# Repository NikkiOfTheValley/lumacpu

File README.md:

# lumacpu
LumaCPU is a custom SBC created for fun/learning

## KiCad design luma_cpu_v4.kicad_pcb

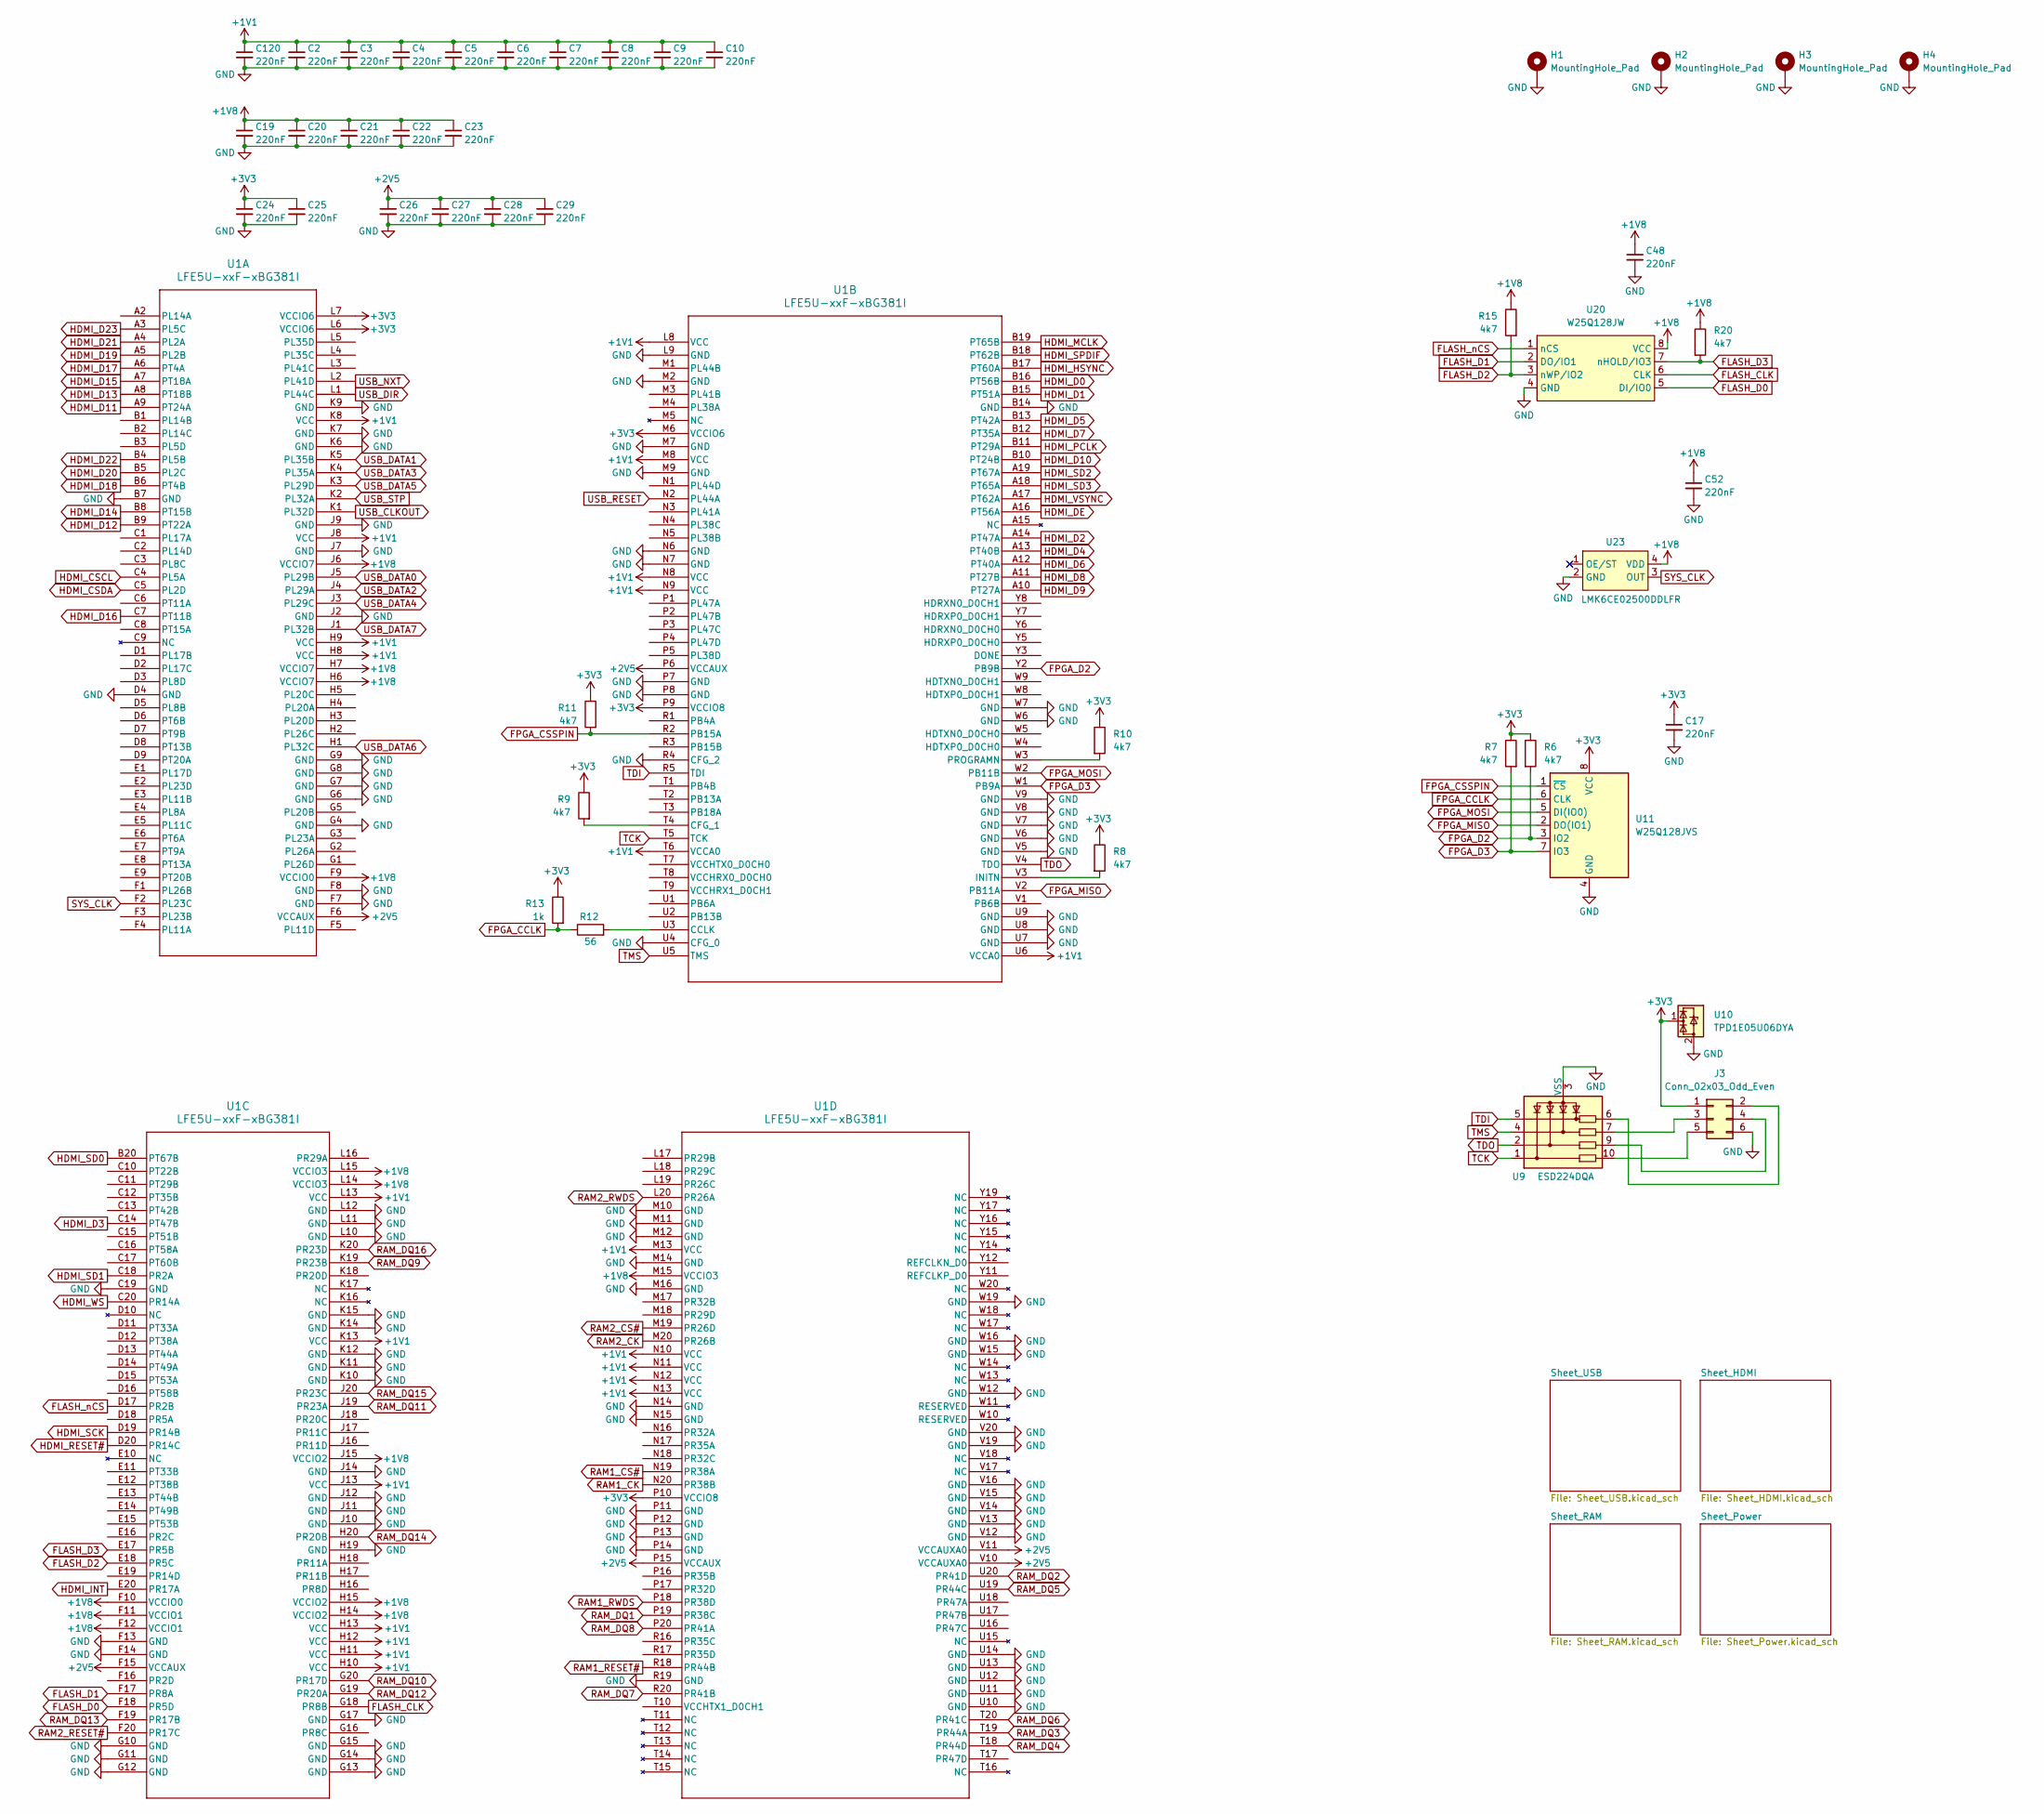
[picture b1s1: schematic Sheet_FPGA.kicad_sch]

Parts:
C2, C3, C4, C5, C6, C7, C8, C9, C10, C17, C19, C20, C21, C22, C23, C24, C25, C26, C27, C28, C29, C48, C52, C120: 220nF; C_0201_0603Metric_Pad0.64x0.40mm_HandSolder
H1, H2, H3, H4: MountingHole_Pad; MountingHole_1.2mm_M1_Pad
J3: Conn_02x03_Odd_Even; PinHeader_2x03_P2.54mm_Vertical
R6, R7, R8, R9, R10, R11, R15, R20: 4k7; R_0402_1005Metric_Pad0.72x0.64mm_HandSolder
R12: 56; R_0402_1005Metric_Pad0.72x0.64mm_HandSolder
R13: 1k; R_0402_1005Metric_Pad0.72x0.64mm_HandSolder
U1: LFE5U-xxF-xBG381I; CABGA381_LAT
U9: ESD224DQA; Diodes_UDFN-10_1.0x2.5mm_P0.5mm
U10: TPD1E05U06DYA; D_SOD-523
U11: W25Q128JVS; SOIC-8_5.23x5.23mm_P1.27mm
U20: W25Q128JW; SOIC-8W_5.3x5.3mm_P1.27mm
U23: LMK6CE02500DDLFR; VSON-4_2.5x2mm_P1.5mm

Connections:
+1V1: C2.1, C3.1, C4.1, C5.1, C6.1, C7.1, C8.1, C9.1, C10.1, U1.H8 (VCC), U1.H9 (VCC), U1.H10 (VCC), U1.H11 (VCC), U1.H12 (VCC), U1.H13 (VCC), U1.J8 (VCC), U1.J13 (VCC), U1.K8 (VCC), U1.K13 (VCC), U1.L8 (VCC), U1.L13 (VCC), U1.M8 (VCC), U1.M13 (VCC), U1.N8 (VCC), U1.N9 (VCC), U1.N10 (VCC), U1.N11 (VCC), U1.N12 (VCC), U1.N13 (VCC), U1.T6 (VCCA0), U1.U6 (VCCA0); also elsewhere on the board
+1V8: C19.1, C20.1, C21.1, C22.1, C23.1, C48.1, C52.1, R15.1, R20.1, U1.F9 (VCCIO0), U1.F10 (VCCIO0), U1.F11 (VCCIO1), U1.F12 (VCCIO1), U1.H6 (VCCIO7), U1.H7 (VCCIO7), U1.H14 (VCCIO2), U1.H15 (VCCIO2), U1.J6 (VCCIO7), U1.J15 (VCCIO2), U1.L14 (VCCIO3), U1.L15 (VCCIO3), U1.M15 (VCCIO3), U20.8 (VCC), U23.4 (VDD); also elsewhere on the board
+2V5: C26.1, C27.1, C28.1, C29.1, U1.F6 (VCCAUX), U1.F15 (VCCAUX), U1.P6 (VCCAUX), U1.P15 (VCCAUX), U1.V10 (VCCAUXA0), U1.V11 (VCCAUXA0); also elsewhere on the board
+3V3: C17.1, C24.1, C25.1, J3.1, R6.1, R7.1, R8.1, R9.1, R10.1, R11.1, R13.1, U1.L6 (VCCIO6), U1.L7 (VCCIO6), U1.M6 (VCCIO6), U1.P9 (VCCIO8), U1.P10 (VCCIO8), U10.1 (I/O), U11.8 (VCC); also elsewhere on the board
FLASH_CLK: U1.G18 (PR8B), U20.6 (CLK)
FLASH_D0: U1.F18 (PR5D), U20.5 (DI/IO0)
FLASH_D1: U1.F17 (PR8A), U20.2 (DO/IO1)
FLASH_D2: R15.2, U1.E18 (PR5C), U20.3 (nWP/IO2)
FLASH_D3: R20.2, U1.E17 (PR5B), U20.7 (nHOLD/IO3)
FLASH_nCS: U1.D17 (PR2B), U20.1 (nCS)
FPGA_CCLK: R12.1, R13.2, U11.6 (CLK)
FPGA_CSSPIN: R11.2, U1.R2 (PB15A), U11.1 (~CS)
FPGA_D2: R6.2, U1.Y2 (PB9B), U11.3 (IO2)
FPGA_D3: R7.2, U1.W1 (PB9A), U11.7 (IO3)
FPGA_MISO: U1.V2 (PB11A), U11.2 (DO(IO1))
FPGA_MOSI: U1.W2 (PB11B), U11.5 (DI(IO0))
GND: C2.2, C3.2, C4.2, C5.2, C6.2, C7.2, C8.2, C9.2, C10.2, C17.2, C19.2, C20.2, C21.2, C22.2, C23.2, C24.2, C25.2, C26.2, C27.2, C28.2, C29.2, C48.2, C52.2, H1.1, H2.1, H3.1, H4.1, J3.6, U1.B7 (GND), U1.B14 (GND), U1.C19 (GND), U1.D4 (GND), U1.F7 (GND), U1.F8 (GND), U1.F13 (GND), U1.F14 (GND), U1.G4 (GND), U1.G6 (GND), U1.G7 (GND), U1.G8 (GND), U1.G9 (GND), U1.G10 (GND), U1.G11 (GND), U1.G12 (GND), U1.G13 (GND), U1.G14 (GND), U1.G15 (GND), U1.G17 (GND), U1.H19 (GND), U1.J2 (GND), U1.J7 (GND), U1.J9 (GND), U1.J10 (GND), U1.J11 (GND), U1.J12 (GND), U1.J14 (GND), U1.K6 (GND), U1.K7 (GND), U1.K9 (GND), U1.K10 (GND), U1.K11 (GND), U1.K12 (GND), U1.K14 (GND), U1.K15 (GND), U1.L9 (GND), U1.L10 (GND), U1.L11 (GND), U1.L12 (GND), U1.M2 (GND), U1.M7 (GND), U1.M9 (GND), U1.M10 (GND), U1.M11 (GND), U1.M12 (GND), U1.M14 (GND), U1.M16 (GND), U1.N6 (GND), U1.N7 (GND), U1.N14 (GND), U1.N15 (GND), U1.P7 (GND), U1.P8 (GND), U1.P11 (GND), U1.P12 (GND), U1.P13 (GND), U1.P14 (GND), U1.R4 (CFG_2), U1.R19 (GND), U1.U4 (CFG_0), U1.U7 (GND), U1.U8 (GND), U1.U9 (GND), U1.U10 (GND), U1.U11 (GND), U1.U12 (GND), U1.U13 (GND), U1.U14 (GND), U1.V5 (GND), U1.V6 (GND), U1.V7 (GND), U1.V8 (GND), U1.V9 (GND), U1.V12 (GND), U1.V13 (GND), U1.V14 (GND), U1.V15 (GND), U1.V16 (GND), U1.V19 (GND), U1.V20 (GND), U1.W6 (GND), U1.W7 (GND), U1.W12 (GND), U1.W15 (GND), U1.W16 (GND), U1.W19 (GND), U9.3 (VSS), U9.8 (VSS), U10.2 (GND), U11.4 (GND), U20.4 (GND), U23.2 (GND); also elsewhere on the board
HDMI_CSCL: U1.C4 (PL5A); also elsewhere on the board
HDMI_CSDA: U1.C5 (PL2D); also elsewhere on the board
HDMI_D0: U1.B16 (PT56B); also elsewhere on the board
HDMI_D1: U1.B15 (PT51A); also elsewhere on the board
HDMI_D2: U1.A14 (PT47A); also elsewhere on the board
HDMI_D3: U1.C14 (PT47B); also elsewhere on the board
HDMI_D4: U1.A13 (PT40B); also elsewhere on the board
HDMI_D5: U1.B13 (PT42A); also elsewhere on the board
HDMI_D6: U1.A12 (PT40A); also elsewhere on the board
HDMI_D7: U1.B12 (PT35A); also elsewhere on the board
HDMI_D8: U1.A11 (PT27B); also elsewhere on the board
HDMI_D9: U1.A10 (PT27A); also elsewhere on the board
HDMI_D10: U1.B10 (PT24B); also elsewhere on the board
HDMI_D11: U1.A9 (PT24A); also elsewhere on the board
HDMI_D12: U1.B9 (PT22A); also elsewhere on the board
HDMI_D13: U1.A8 (PT18B); also elsewhere on the board
HDMI_D14: U1.B8 (PT15B); also elsewhere on the board
HDMI_D15: U1.A7 (PT18A); also elsewhere on the board
HDMI_D16: U1.C7 (PT11B); also elsewhere on the board
HDMI_D17: U1.A6 (PT4A); also elsewhere on the board
HDMI_D18: U1.B6 (PT4B); also elsewhere on the board
HDMI_D19: U1.A5 (PL2B); also elsewhere on the board
HDMI_D20: U1.B5 (PL2C); also elsewhere on the board
HDMI_D21: U1.A4 (PL2A); also elsewhere on the board
HDMI_D22: U1.B4 (PL5B); also elsewhere on the board
HDMI_D23: U1.A3 (PL5C); also elsewhere on the board
HDMI_DE: U1.A16 (PT56A); also elsewhere on the board
HDMI_HSYNC: U1.B17 (PT60A); also elsewhere on the board
HDMI_INT: U1.E20 (PR17A); also elsewhere on the board
HDMI_MCLK: U1.B19 (PT65B); also elsewhere on the board
HDMI_PCLK: U1.B11 (PT29A); also elsewhere on the board
HDMI_RESET#: U1.D20 (PR14C); also elsewhere on the board
HDMI_SCK: U1.D19 (PR14B); also elsewhere on the board
HDMI_SD0: U1.B20 (PT67B); also elsewhere on the board
HDMI_SD1: U1.C18 (PR2A); also elsewhere on the board
HDMI_SD2: U1.A19 (PT67A); also elsewhere on the board
HDMI_SD3: U1.A18 (PT65A); also elsewhere on the board
HDMI_SPDIF: U1.B18 (PT62B); also elsewhere on the board
HDMI_VSYNC: U1.A17 (PT62A); also elsewhere on the board
HDMI_WS: U1.C20 (PR14A); also elsewhere on the board
unnamed: J3.2, U9.6
unnamed: J3.3, U9.7
unnamed: J3.4, U9.9
unnamed: J3.5, U9.10
unnamed: R12.2, U1.U3 (CCLK)
unnamed: R9.2, U1.T4 (CFG_1)
unnamed: R8.2, U1.V3 (INITN)
unnamed: R10.2, U1.W3 (PROGRAMN)
RAM1_CK: U1.N20 (PR38B); also elsewhere on the board
RAM1_CS#: U1.N19 (PR38A); also elsewhere on the board
RAM1_RESET#: U1.R18 (PR44B); also elsewhere on the board
RAM1_RWDS: U1.P18 (PR38D); also elsewhere on the board
RAM2_CK: U1.M20 (PR26B); also elsewhere on the board
RAM2_CS#: U1.M19 (PR26D); also elsewhere on the board
RAM2_RESET#: U1.F20 (PR17C); also elsewhere on the board
RAM2_RWDS: U1.L20 (PR26A); also elsewhere on the board
RAM_DQ1: U1.P19 (PR38C); also elsewhere on the board
RAM_DQ2: U1.U20 (PR41D); also elsewhere on the board
RAM_DQ3: U1.T19 (PR44A); also elsewhere on the board
RAM_DQ4: U1.T18 (PR44D); also elsewhere on the board
RAM_DQ5: U1.U19 (PR44C); also elsewhere on the board
RAM_DQ6: U1.T20 (PR41C); also elsewhere on the board
RAM_DQ7: U1.R20 (PR41B); also elsewhere on the board
RAM_DQ8: U1.P20 (PR41A); also elsewhere on the board
RAM_DQ9: U1.K19 (PR23B); also elsewhere on the board
RAM_DQ10: U1.G20 (PR17D); also elsewhere on the board
RAM_DQ11: U1.J19 (PR23A); also elsewhere on the board
RAM_DQ12: U1.G19 (PR20A); also elsewhere on the board
RAM_DQ13: U1.F19 (PR17B); also elsewhere on the board
RAM_DQ14: U1.H20 (PR20B); also elsewhere on the board
RAM_DQ15: U1.J20 (PR23C); also elsewhere on the board
RAM_DQ16: U1.K20 (PR23D); also elsewhere on the board
SYS_CLK: U1.F2 (PL23C), U23.3 (OUT)
TCK: U1.T5 (TCK), U9.1
TDI: U1.R5 (TDI), U9.5
TDO: U1.V4 (TDO), U9.2
TMS: U1.U5 (TMS), U9.4
USB_CLKOUT: U1.K1 (PL32D); also elsewhere on the board
USB_DATA0: U1.J5 (PL29B); also elsewhere on the board
USB_DATA1: U1.K5 (PL35B); also elsewhere on the board
USB_DATA2: U1.J4 (PL29A); also elsewhere on the board
USB_DATA3: U1.K4 (PL35A); also elsewhere on the board
USB_DATA4: U1.J3 (PL29C); also elsewhere on the board
USB_DATA5: U1.K3 (PL29D); also elsewhere on the board
USB_DATA6: U1.H1 (PL32C); also elsewhere on the board
USB_DATA7: U1.J1 (PL32B); also elsewhere on the board
USB_DIR: U1.L1 (PL44C); also elsewhere on the board
USB_NXT: U1.L2 (PL41D); also elsewhere on the board
USB_RESET: U1.N2 (PL44A); also elsewhere on the board
USB_STP: U1.K2 (PL32A); also elsewhere on the board

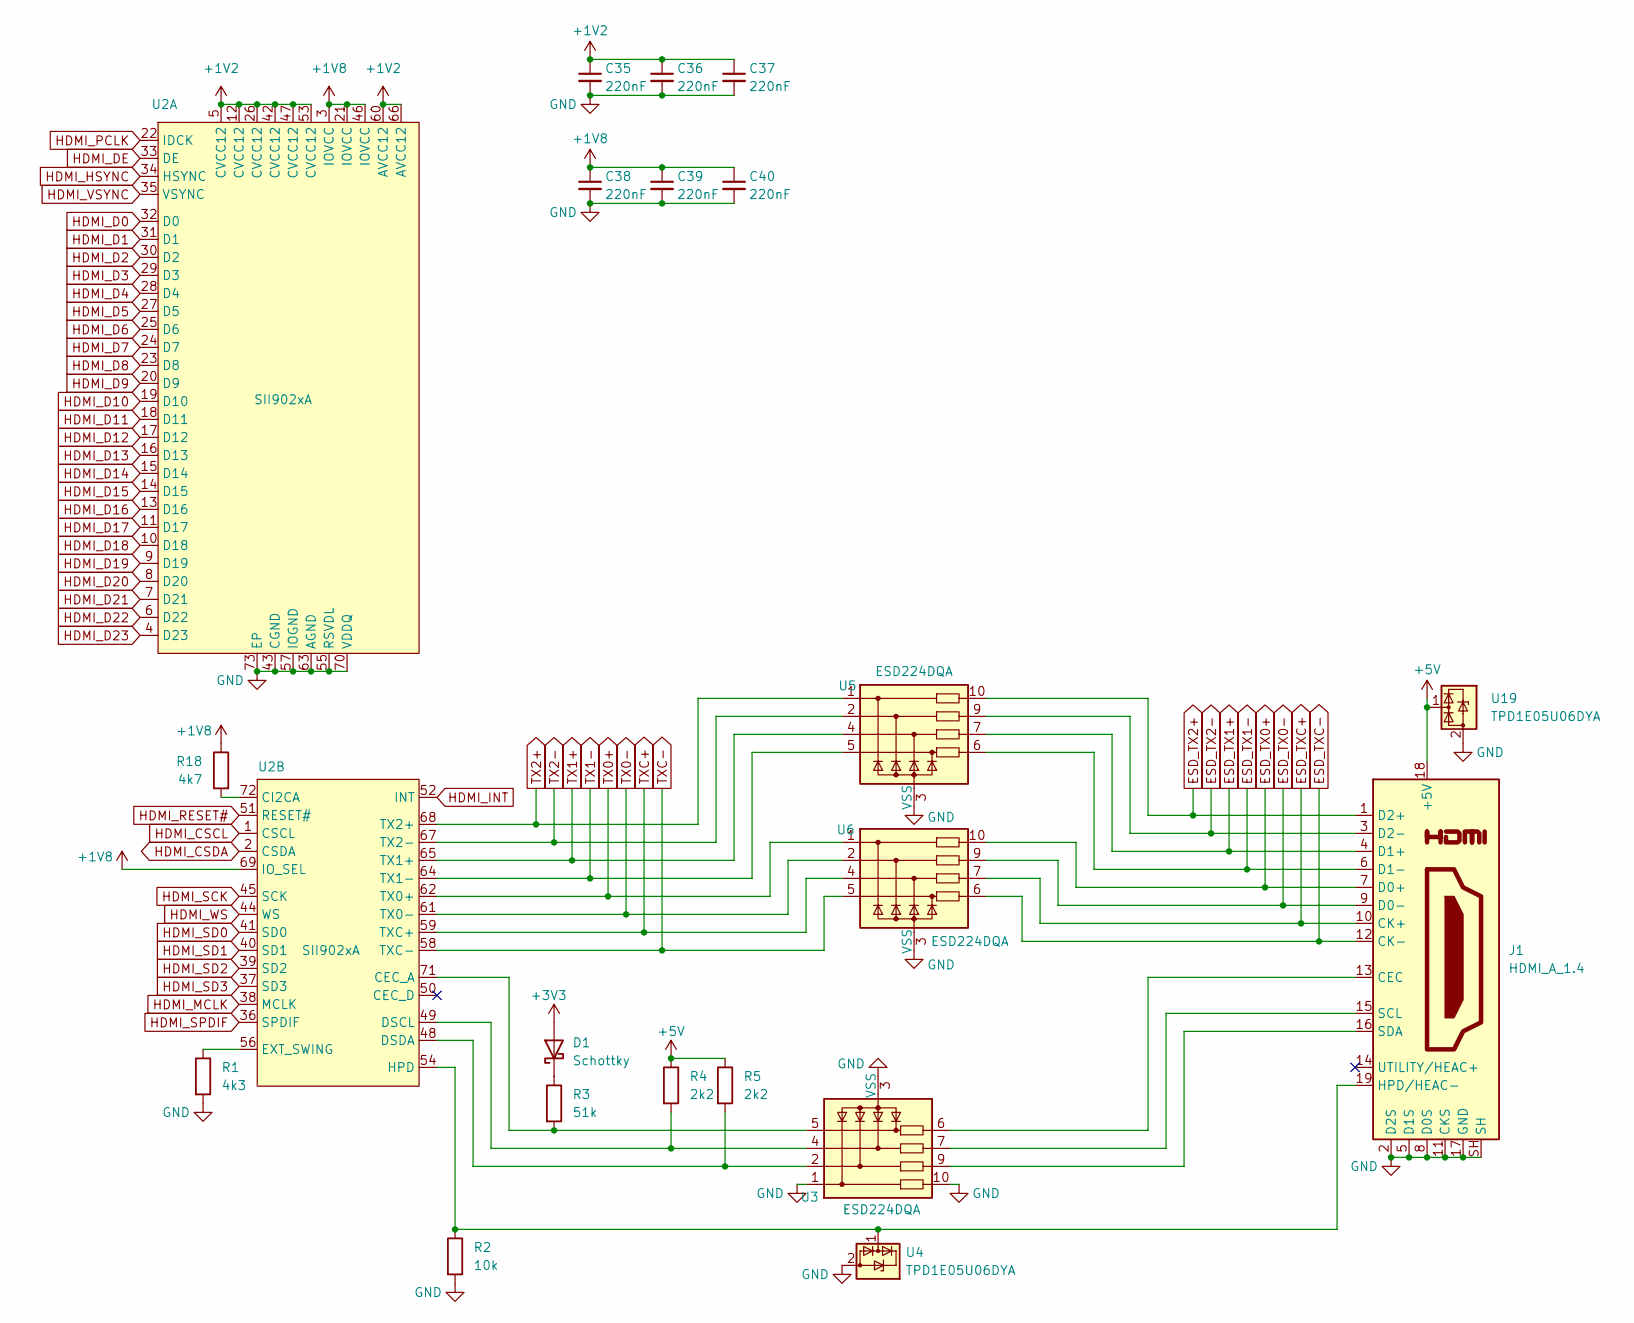
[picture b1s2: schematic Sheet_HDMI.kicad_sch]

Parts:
C35, C36, C37, C38, C39, C40: 220nF; C_0201_0603Metric_Pad0.64x0.40mm_HandSolder
D1: Schottky; D_SOD-523
J1: HDMI_A_1.4; HDMI_A_Amphenol_10029449-x01xLF_Horizontal
R1: 4k3; R_0402_1005Metric_Pad0.72x0.64mm_HandSolder
R2: 10k; R_0402_1005Metric_Pad0.72x0.64mm_HandSolder
R3: 51k; R_0402_1005Metric_Pad0.72x0.64mm_HandSolder
R4, R5: 2k2; R_0402_1005Metric_Pad0.72x0.64mm_HandSolder
R18: 4k7; R_0402_1005Metric_Pad0.72x0.64mm_HandSolder
U2: SII902xA; QFN-72-1EP_10x10mm_P0.5mm_EP6x6mm
U3, U5, U6: ESD224DQA; Diodes_UDFN-10_1.0x2.5mm_P0.5mm
U4, U19: TPD1E05U06DYA; D_SOD-523

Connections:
+1V2: C35.1, C36.1, C37.1, U2.5 (CVCC12), U2.12 (CVCC12), U2.26 (CVCC12), U2.42 (CVCC12), U2.47 (CVCC12), U2.53 (CVCC12), U2.60 (AVCC12), U2.66 (AVCC12); also elsewhere on the board
+1V8: C38.1, C39.1, C40.1, R18.1, U2.3 (IOVCC), U2.21 (IOVCC), U2.46 (IOVCC), U2.69 (IO_SEL); also elsewhere on the board
+3V3: D1.2 (A); also elsewhere on the board
+5V: J1.18 (+5V), R4.1, R5.1, U19.1 (I/O); also elsewhere on the board
ESD_TX0+: J1.7 (D0+), U6.10
ESD_TX0-: J1.9 (D0-), U6.9
ESD_TX1+: J1.4 (D1+), U5.7
ESD_TX1-: J1.6 (D1-), U5.6
ESD_TX2+: J1.1 (D2+), U5.10
ESD_TX2-: J1.3 (D2-), U5.9
ESD_TXC+: J1.10 (CK+), U6.7
ESD_TXC-: J1.12 (CK-), U6.6
GND: C35.2, C36.2, C37.2, C38.2, C39.2, C40.2, J1.2 (D2S), J1.5 (D1S), J1.8 (D0S), J1.11 (CKS), J1.17 (GND), J1.SH, R1.2, R2.2, U2.43 (CGND), U2.55 (RSVDL), U2.57 (IOGND), U2.63 (AGND), U2.70 (VDDQ), U2.73 (EP), U3.1, U3.3 (VSS), U3.8 (VSS), U3.10, U4.2 (GND), U5.3 (VSS), U5.8 (VSS), U6.3 (VSS), U6.8 (VSS), U19.2 (GND); also elsewhere on the board
HDMI_CSCL: U2.1 (CSCL); also elsewhere on the board
HDMI_CSDA: U2.2 (CSDA); also elsewhere on the board
HDMI_D0: U2.32 (D0); also elsewhere on the board
HDMI_D1: U2.31 (D1); also elsewhere on the board
HDMI_D2: U2.30 (D2); also elsewhere on the board
HDMI_D3: U2.29 (D3); also elsewhere on the board
HDMI_D4: U2.28 (D4); also elsewhere on the board
HDMI_D5: U2.27 (D5); also elsewhere on the board
HDMI_D6: U2.25 (D6); also elsewhere on the board
HDMI_D7: U2.24 (D7); also elsewhere on the board
HDMI_D8: U2.23 (D8); also elsewhere on the board
HDMI_D9: U2.20 (D9); also elsewhere on the board
HDMI_D10: U2.19 (D10); also elsewhere on the board
HDMI_D11: U2.18 (D11); also elsewhere on the board
HDMI_D12: U2.17 (D12); also elsewhere on the board
HDMI_D13: U2.16 (D13); also elsewhere on the board
HDMI_D14: U2.15 (D14); also elsewhere on the board
HDMI_D15: U2.14 (D15); also elsewhere on the board
HDMI_D16: U2.13 (D16); also elsewhere on the board
HDMI_D17: U2.11 (D17); also elsewhere on the board
HDMI_D18: U2.10 (D18); also elsewhere on the board
HDMI_D19: U2.9 (D19); also elsewhere on the board
HDMI_D20: U2.8 (D20); also elsewhere on the board
HDMI_D21: U2.7 (D21); also elsewhere on the board
HDMI_D22: U2.6 (D22); also elsewhere on the board
HDMI_D23: U2.4 (D23); also elsewhere on the board
HDMI_DE: U2.33 (DE); also elsewhere on the board
HDMI_HSYNC: U2.34 (HSYNC); also elsewhere on the board
HDMI_INT: U2.52 (INT); also elsewhere on the board
HDMI_MCLK: U2.38 (MCLK); also elsewhere on the board
HDMI_PCLK: U2.22 (IDCK); also elsewhere on the board
HDMI_RESET#: U2.51 (RESET#); also elsewhere on the board
HDMI_SCK: U2.45 (SCK); also elsewhere on the board
HDMI_SD0: U2.41 (SD0); also elsewhere on the board
HDMI_SD1: U2.40 (SD1); also elsewhere on the board
HDMI_SD2: U2.39 (SD2); also elsewhere on the board
HDMI_SD3: U2.37 (SD3); also elsewhere on the board
HDMI_SPDIF: U2.36 (SPDIF); also elsewhere on the board
HDMI_VSYNC: U2.35 (VSYNC); also elsewhere on the board
HDMI_WS: U2.44 (WS); also elsewhere on the board
unnamed: D1.1 (K), R3.1
unnamed: J1.13 (CEC), U3.6
unnamed: J1.19 (HPD/HEAC-), R2.1, U2.54 (HPD), U4.1 (I/O)
unnamed: J1.15 (SCL), U3.7
unnamed: J1.16 (SDA), U3.9
unnamed: R3.2, U2.71 (CEC_A), U3.5
unnamed: R18.2, U2.72 (CI2CA)
unnamed: R4.2, U2.49 (DSCL), U3.4
unnamed: R5.2, U2.48 (DSDA), U3.2
unnamed: R1.1, U2.56 (EXT_SWING)
TX0+: U2.62 (TX0+), U6.1
TX0-: U2.61 (TX0-), U6.2
TX1+: U2.65 (TX1+), U5.4
TX1-: U2.64 (TX1-), U5.5
TX2+: U2.68 (TX2+), U5.1
TX2-: U2.67 (TX2-), U5.2
TXC+: U2.59 (TXC+), U6.4
TXC-: U2.58 (TXC-), U6.5

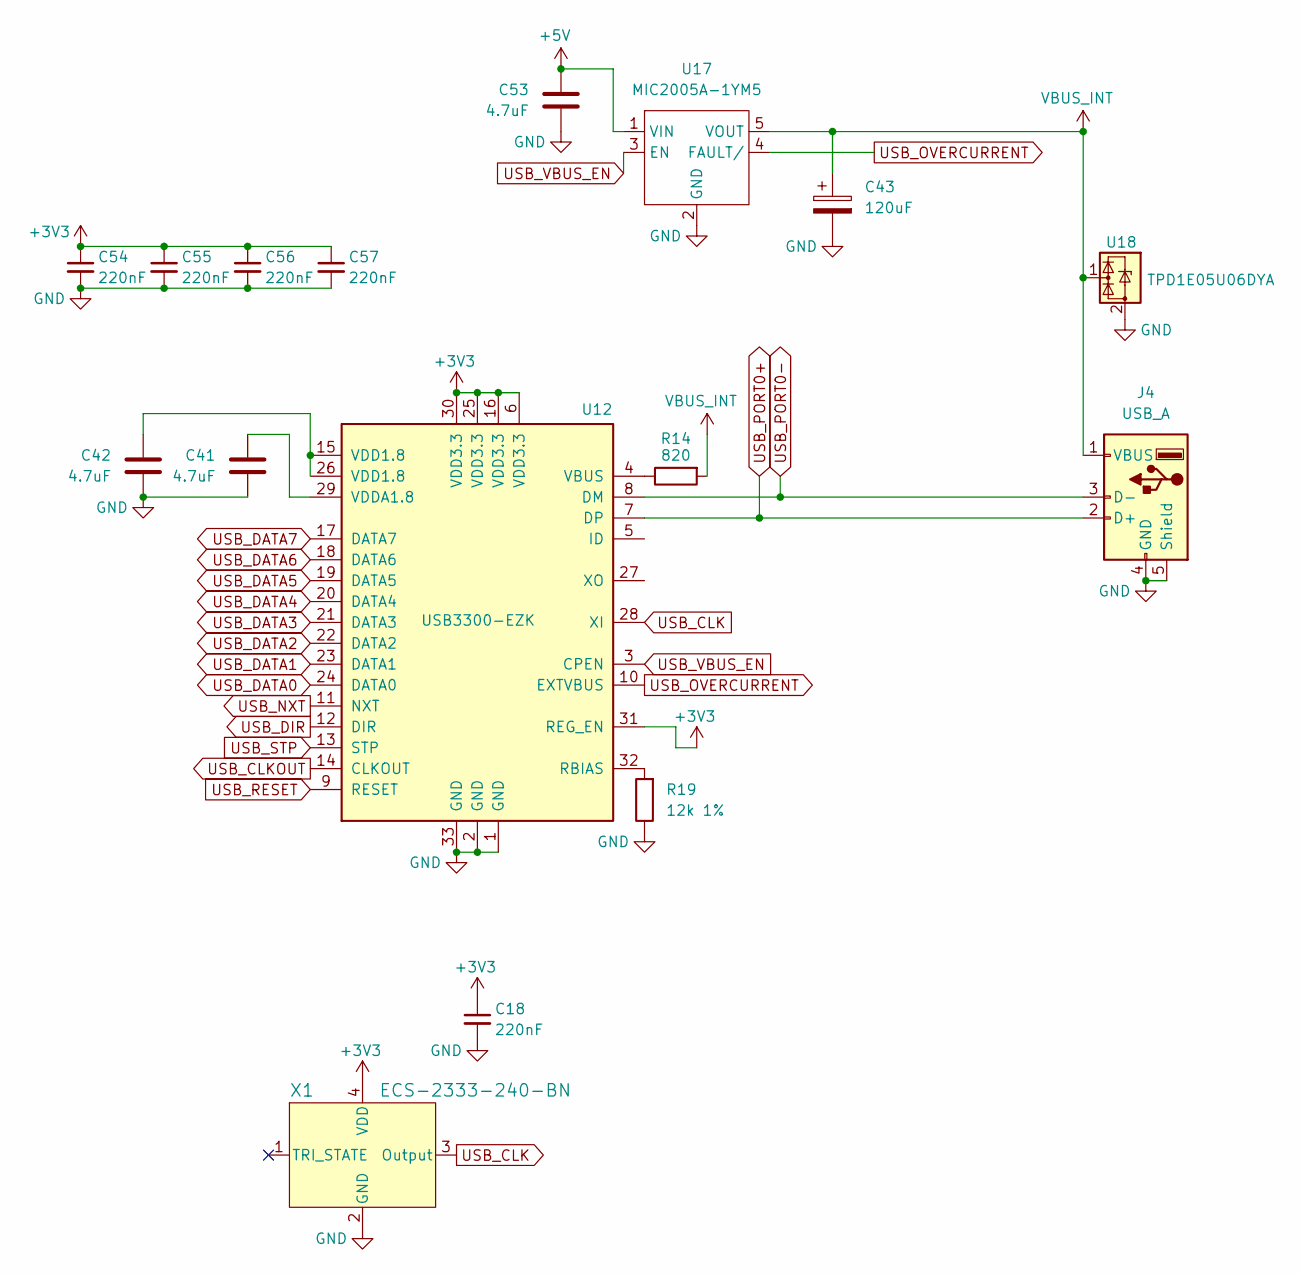
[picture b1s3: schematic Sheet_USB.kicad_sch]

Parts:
C18, C54, C55, C56, C57: 220nF; C_0201_0603Metric_Pad0.64x0.40mm_HandSolder
C41, C42, C53: 4.7uF; C_0402_1005Metric_Pad0.74x0.62mm_HandSolder
C43: 120uF; CP_Elec_6.3x5.8
J4: USB_A; USB_A_Molex_67643_Horizontal
R14: 820; R_0402_1005Metric_Pad0.72x0.64mm_HandSolder
R19: 12k 1%; R_0402_1005Metric_Pad0.72x0.64mm_HandSolder
U12: USB3300-EZK; QFN-32-1EP_5x5mm_P0.5mm_EP3.45x3.45mm
U17: MIC2005A-1YM5; SOT-23-5
U18: TPD1E05U06DYA; D_SOD-523
X1: ECS-2333-240-BN; ECS-2333_ECS

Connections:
+3V3: C18.1, C54.1, C55.1, C56.1, C57.1, U12.6 (VDD3.3), U12.16 (VDD3.3), U12.25 (VDD3.3), U12.30 (VDD3.3), U12.31 (REG_EN), X1.4 (VDD); also elsewhere on the board
+5V: C53.1, U17.1 (VIN); also elsewhere on the board
GND: C18.2, C41.2, C42.2, C43.2, C53.2, C54.2, C55.2, C56.2, C57.2, J4.4 (GND), J4.5 (Shield), R19.1, U12.1 (GND), U12.2 (GND), U12.33 (GND), U17.2 (GND), U18.2 (GND), X1.2 (GND); also elsewhere on the board
unnamed: C42.1, U12.15 (VDD1.8), U12.26 (VDD1.8)
unnamed: R19.2, U12.32 (RBIAS)
unnamed: R14.1, U12.4 (VBUS)
unnamed: C41.1, U12.29 (VDDA1.8)
USB_CLK: U12.28 (XI), X1.3 (Output)
USB_CLKOUT: U12.14 (CLKOUT); also elsewhere on the board
USB_DATA0: U12.24 (DATA0); also elsewhere on the board
USB_DATA1: U12.23 (DATA1); also elsewhere on the board
USB_DATA2: U12.22 (DATA2); also elsewhere on the board
USB_DATA3: U12.21 (DATA3); also elsewhere on the board
USB_DATA4: U12.20 (DATA4); also elsewhere on the board
USB_DATA5: U12.19 (DATA5); also elsewhere on the board
USB_DATA6: U12.18 (DATA6); also elsewhere on the board
USB_DATA7: U12.17 (DATA7); also elsewhere on the board
USB_DIR: U12.12 (DIR); also elsewhere on the board
USB_NXT: U12.11 (NXT); also elsewhere on the board
USB_OVERCURRENT: U12.10 (EXTVBUS), U17.4 (FAULT/)
USB_PORT0+: J4.2 (D+), U12.7 (DP)
USB_PORT0-: J4.3 (D-), U12.8 (DM)
USB_RESET: U12.9 (RESET); also elsewhere on the board
USB_STP: U12.13 (STP); also elsewhere on the board
USB_VBUS_EN: U12.3 (CPEN), U17.3 (EN)
VBUS_INT: C43.1, J4.1 (VBUS), R14.2, U17.5 (VOUT), U18.1 (I/O)

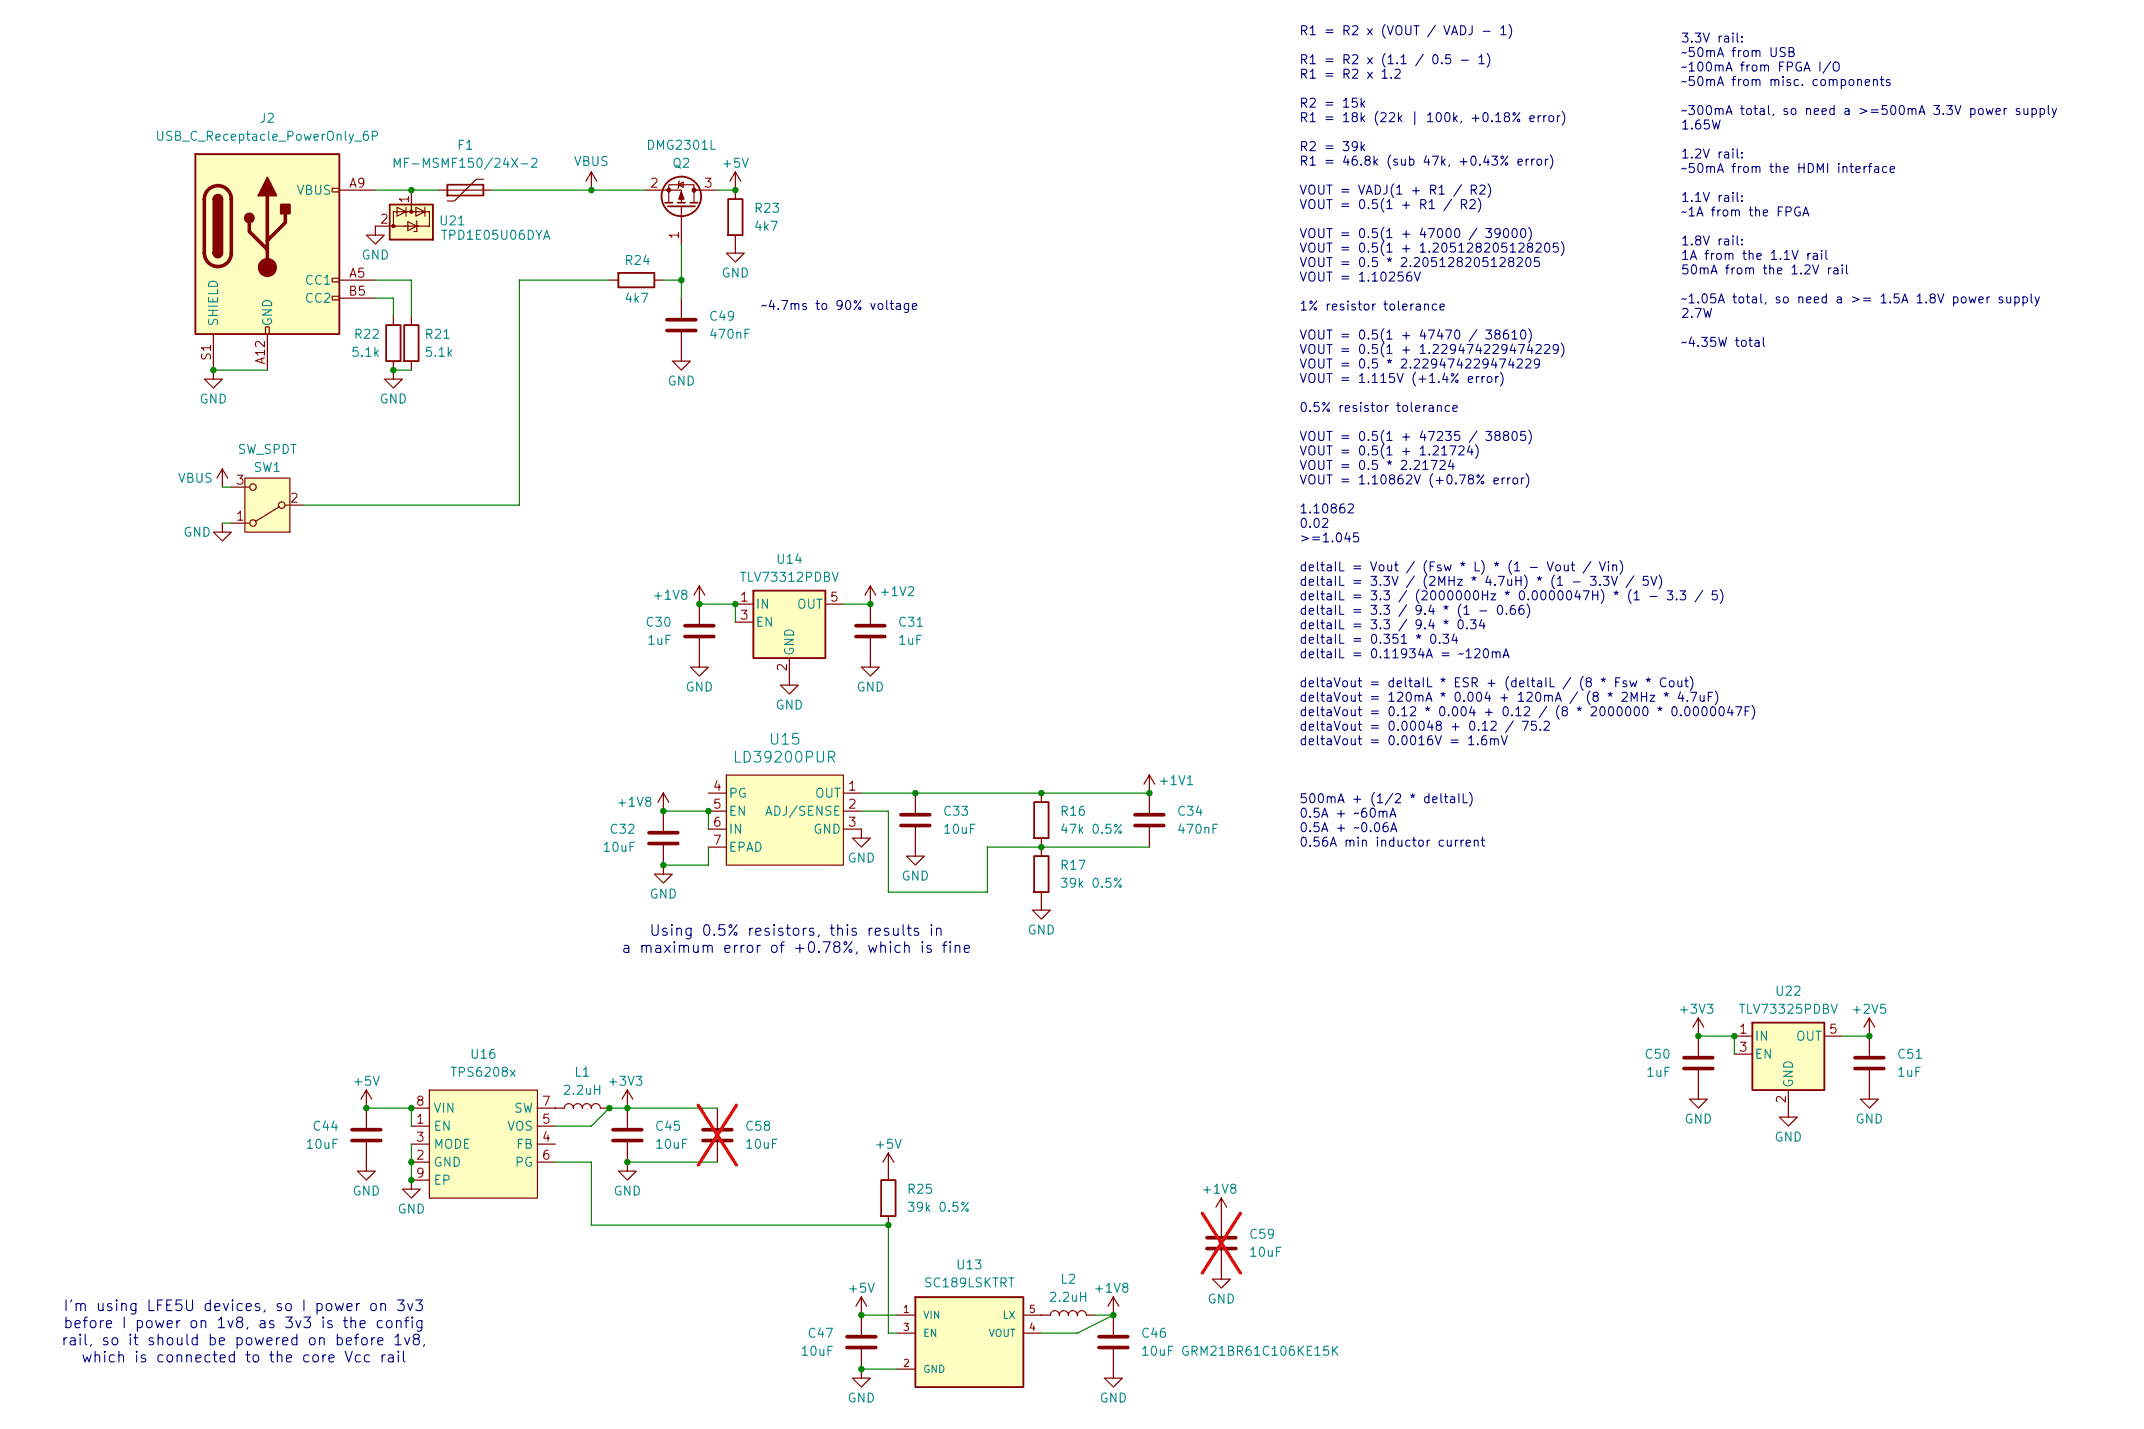
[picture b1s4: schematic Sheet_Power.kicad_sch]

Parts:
C30, C31, C50, C51: 1uF; C_0402_1005Metric_Pad0.74x0.62mm_HandSolder
C32, C33, C44, C45, C47: 10uF; C_0603_1608Metric_Pad1.08x0.95mm_HandSolder
C34, C49: 470nF; C_0402_1005Metric_Pad0.74x0.62mm_HandSolder
C46: 10uF GRM21BR61C106KE15K; C_0805_2012Metric_Pad1.18x1.45mm_HandSolder
C58, C59: 10uF; C_0603_1608Metric_Pad1.08x0.95mm_HandSolder; not fitted
F1: MF-MSMF150/24X-2; Fuse_1812_4532Metric_Pad1.30x3.40mm_HandSolder
J2: USB_C_Receptacle_PowerOnly_6P; USB_C_Receptacle_GCT_USB4125-xx-x_6P_TopMnt_Horizontal
L1, L2: 2.2uH; IND_TAIYO_NRS4018_TAY
Q2: DMG2301L; SOT-23
R16: 47k 0.5%; R_0402_1005Metric_Pad0.72x0.64mm_HandSolder
R17, R25: 39k 0.5%; R_0402_1005Metric_Pad0.72x0.64mm_HandSolder
R21, R22: 5.1k; R_0402_1005Metric_Pad0.72x0.64mm_HandSolder
R23, R24: 4k7; R_0402_1005Metric_Pad0.72x0.64mm_HandSolder
SW1: SW_SPDT; PinSocket_1x03_P2.54mm_Vertical
U13: SC189LSKTRT; SOT95P280X145-5N
U14: TLV73312PDBV; SOT-23-5
U15: LD39200PUR; DFN6_3P1X3P1X0P95_STM
U16: TPS6208x; WSON-8-1EP_2x2mm_P0.5mm_EP0.9x1.6mm
U21: TPD1E05U06DYA; D_SOD-523
U22: TLV73325PDBV; SOT-23-5

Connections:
+1V1: C33.1, C34.1, R16.1, U15.1 (OUT); also elsewhere on the board
+1V2: C31.1, U14.5 (OUT); also elsewhere on the board
+1V8: C30.1, C32.1, C46.1, C59.1, L2.2, U13.4 (VOUT), U14.1 (IN), U14.3 (EN), U15.5 (EN), U15.6 (IN); also elsewhere on the board
+2V5: C51.1, U22.5 (OUT); also elsewhere on the board
+3V3: C45.1, C50.1, C58.1, L1.2, U16.5 (VOS), U22.1 (IN), U22.3 (EN); also elsewhere on the board
+5V: C44.1, C47.1, Q2.3 (D), R23.1, R25.1, U13.1 (VIN), U16.1 (EN), U16.8 (VIN); also elsewhere on the board
GND: C30.2, C31.2, C32.2, C33.2, C44.2, C45.2, C46.2, C47.2, C49.2, C50.2, C51.2, C58.2, C59.2, J2.A12 (GND), J2.B12 (GND), J2.S1 (SHIELD), R17.2, R21.2, R22.2, R23.2, SW1.1 (A), U13.2 (GND), U14.2 (GND), U15.3 (GND), U15.7 (EPAD), U16.2 (GND), U16.3 (MODE), U16.9 (EP), U21.2 (GND), U22.2 (GND); also elsewhere on the board
unnamed: J2.A5 (CC1), R21.1
unnamed: J2.B5 (CC2), R22.1
unnamed: C49.1, Q2.1 (G), R24.1
unnamed: R24.2, SW1.2 (B)
unnamed: R25.2, U13.3 (EN), U16.6 (PG)
unnamed: L2.1, U13.5 (LX)
unnamed: C34.2, R16.2, R17.1, U15.2 (ADJ/SENSE)
unnamed: L1.1, U16.7 (SW)
unnamed: F1.1, J2.A9 (VBUS), J2.B9 (VBUS), U21.1 (I/O)
VBUS: F1.2, Q2.2 (S), SW1.3 (C)

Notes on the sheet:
3.3V rail: ~50mA from USB ~100mA from FPGA I/O ~50mA from misc. components ~300mA total, so need a >=500mA 3.3V power supply 1.65W 1.2V rail: ~50mA from the HDMI interface 1.1V rail: ~1A from the FPGA 1.8V rail: 1A from the 1.1V rail 50mA from the 1.2V rail ~1.05A total, so need a >= 1.5A 1.8V powe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
~4.7ms to 90% voltage
Using 0.5% resistors, this results in a maximum error of +0.78%, which is fine
I'm using LFE5U devices, so I power on 3v3 before I power on 1v8, as 3v3 is the config rail, so it should be powered on before 1v8, which is connected to the core Vcc rail
R1 = R2 x (VOUT / VADJ - 1) R1 = R2 x (1.1 / 0.5 - 1) R1 = R2 x 1.2 R2 = 15k R1 = 18k (22k | 100k, +0.18% error) R2 = 39k R1 = 46.8k (sub 47k, +0.43% error) VOUT = VADJ(1 + R1 / R2) VOUT = 0.5(1 + R1 / R2) VOUT = 0.5(1 + 47000 / 39000) VOUT = 0.5(1 + 1.205128205128205) VOUT = 0.5 * 2.20512820512820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
